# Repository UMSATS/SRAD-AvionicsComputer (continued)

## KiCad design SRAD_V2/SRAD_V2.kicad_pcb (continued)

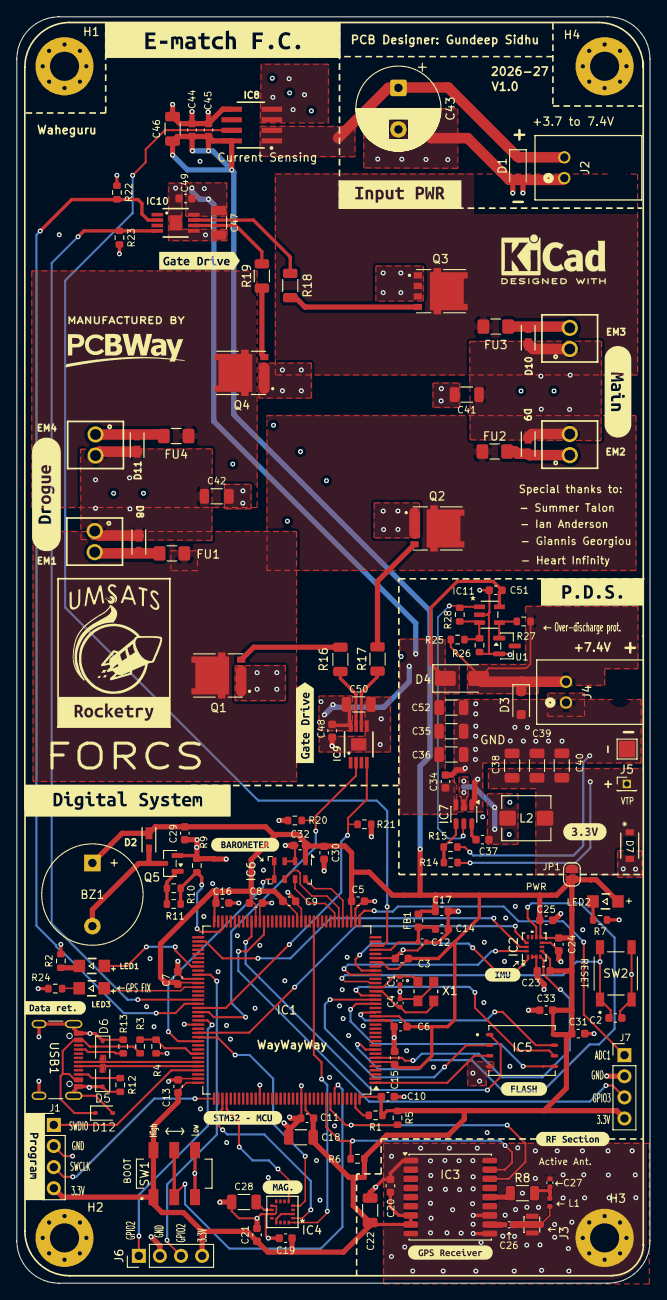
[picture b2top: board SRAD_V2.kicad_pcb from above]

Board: 4 copper layers, 76.2 x 152.4 mm, 159 parts (0 on the bottom side), 87 nets.

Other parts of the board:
kibuzzard-6A3D75FD: G***; kibuzzard-6A3D75FD
kibuzzard-6A95C1A9: G***; kibuzzard-6A95C1A9
kibuzzard-6A95C5A9: G***; kibuzzard-6A95C5A9
kibuzzard-6A95C150: G***; kibuzzard-6A95C150
kibuzzard-6A95C804: G***; kibuzzard-6A95C804
kibuzzard-6A95CBD7: G***; kibuzzard-6A95CBD7
kibuzzard-6A95CC6E: G***; kibuzzard-6A95CC6E
kibuzzard-6A95CC9C: G***; kibuzzard-6A95CC9C
kibuzzard-6A6394C9: G***; kibuzzard-6A6394C9
kibuzzard-6A6394D1: G***; kibuzzard-6A6394D1
kibuzzard-6A9050F6: G***; kibuzzard-6A9050F6
kibuzzard-6A9704D1: G***; kibuzzard-6A9704D1
kibuzzard-6A876244: G***; kibuzzard-6A876244
kibuzzard-6A982418: G***; kibuzzard-6A982418
kibuzzard-6ABFFFA9: G***; kibuzzard-6ABFFFA9
kibuzzard-6AC0F9EB: G***; kibuzzard-6AC0F9EB
kibuzzard-6AC0FA62: G***; kibuzzard-6AC0FA62
kibuzzard-6AC04A03: G***; kibuzzard-6AC04A03
kibuzzard-6AC049EA: G***; kibuzzard-6AC049EA

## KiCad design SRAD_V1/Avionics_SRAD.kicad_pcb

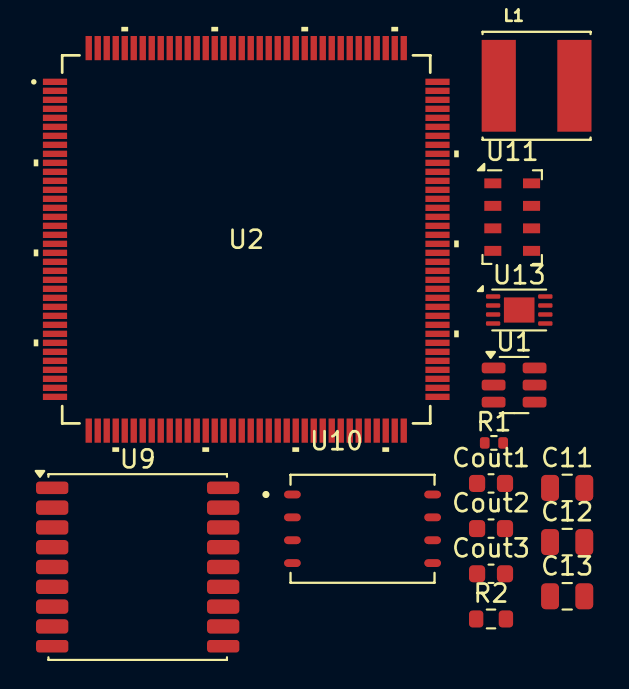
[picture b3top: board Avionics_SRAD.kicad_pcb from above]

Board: 2 copper layers, 15 parts (0 on the bottom side), 7 nets, no tracks yet.

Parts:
C11, C13: 10uF; C_0805_2012Metric
C12: 100nF; C_0805_2012Metric
Cout1, Cout2, Cout3: 22uF; C_0603_1608Metric
L1: 2.2uH; IND_VLS6045EX-2R2N
R1: 33.2k; R_0402_1005Metric
R2: 10k; R_0603_1608Metric
U1: TPS563200; SOT-23-6
U2: STM32F767ZIT6; LQFP144-20x20mm_STM
U9: MAX-M10S; ublox_MAX
U10: AS5F31G04SND-08LIN; SON127P600X800X80-8N
U11: MS5607-02BA; LGA-8_3x5mm_P1.25mm
U13: MCP9808_DFN; DFN-8-1EP_3x2mm_P0.5mm_EP1.7x1.4mm

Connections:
GND: C11.2, C13.2, Cout1.2, Cout2.2, Cout3.2, R2.2, U1.1 (GND), U9.1 (GND), U9.10 (GND), U9.12 (GND), U10.4 (VSS), U11.3 (GND), U13.4 (GND)
unnamed: C12.1, L1.1, U1.2 (SW)
unnamed: C12.2, U1.6 (VBST)
unnamed: R1.2, R2.1, U1.4 (VFB)
unnamed: U11.4 (CSB), U11.5 (CSB)
V3V3: Cout1.1, Cout2.1, Cout3.1, L1.2, R1.1, U9.8 (VCC), U10.8 (VCC), U11.1 (VDD), U13.8 (V_{DD})
VIN: C11.1, C13.1, U1.3 (VIN), U1.5 (EN)

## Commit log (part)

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2025-06-01 Initial commit: upload KiCad Avionics SRAD project
2025-06-01 Add full README with project details
2025-06-03 Updated file names
2025-06-10 Corrected footprint assignment errors
2025-09-23 Updated the structure of the SRAD folder
2025-09-23 Updated SRAD folder structure and schematic
2025-09-23 Add README with project overview and file descriptions
2025-09-23 Updated SRAD_V1 schematic
2026-02-21 added correct models and linked footprints
2026-02-22 Changing file structure for merging in future
2026-02-22 something
2026-02-22 created some basic building blocks as hierarchical sheets
2026-02-23 linked 3-d models
2026-03-01 more changes
2026-03-07 finalish changes
2026-03-08 new connector
2026-03-10 tinkered with the layout
2026-03-16 added text-box for communication protocols in the schematic
2026-03-16 text-box
2026-03-17 added bunch of decoupling capacitors, updated mosfet symbols with KICAD in-built ones etc
2026-03-20 fixed some origin issues on pcb -- working on the PDS
2026-03-21 PDS pcb layout
2026-05-01 PDS routing
2026-05-01 kibuzzard works!
2026-05-02 little tweaks here and there
2026-05-07 updated MCU cad models
2026-05-08 added new IMU to the schematic
2026-05-09 Done with Pin Assignments
2026-05-12 routing for e-match circuit
2026-05-14 added magnometer e-cad model
2026-05-28 sensor routing
2026-06-01 Sensor routing and integration of various systems on the PCB
2026-06-16 more routing
2026-06-21 Updated the buzzer
